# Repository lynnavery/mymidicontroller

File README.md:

# mymidicontroller
Simple 9 knob 10 key midi controller design using teensy and no mux/adc expanders

## Mockup

## BOM
| Qty | Part |
|---|---|
| 1 | Teensy 4.1 with headers |
| 2 | Custom PCB
| 1 | Jumper wires Female/Male 300mm pack of 40 |
| 1 | Strip of standard headers (2.54mm) for 22 total
| 1 | USB A to Micro-B cable |
| 9 | 10K linear pot PTV09A-4020U-B103 |
| 10 | Cherry MX/knockoff switch (any color) |
| 10 | Keycaps |
| 1 | 0.96in OLED I2C 4-pin white character display |
| 1 | Enclosure and front panel (3d printed) |

If I decide to do an expander for the extra teensy io
| Qty | Part |
|---|---|
| 1 | Panel-mount D-sub or aviation connector |
| 6 | Series resistors 220ohm-1k for expander lines |

## Circuit diagram

## References
- https://www.pjrc.com/teensy/td_midi.html
- Library for teensy midi controllers https://github.com/joshnishikawa/MIDIcontroller
- another midi library for teensy https://tomashg.com/?p=854
- another midi library https://tttapa.github.io/Control-Surface/Doxygen/index.html

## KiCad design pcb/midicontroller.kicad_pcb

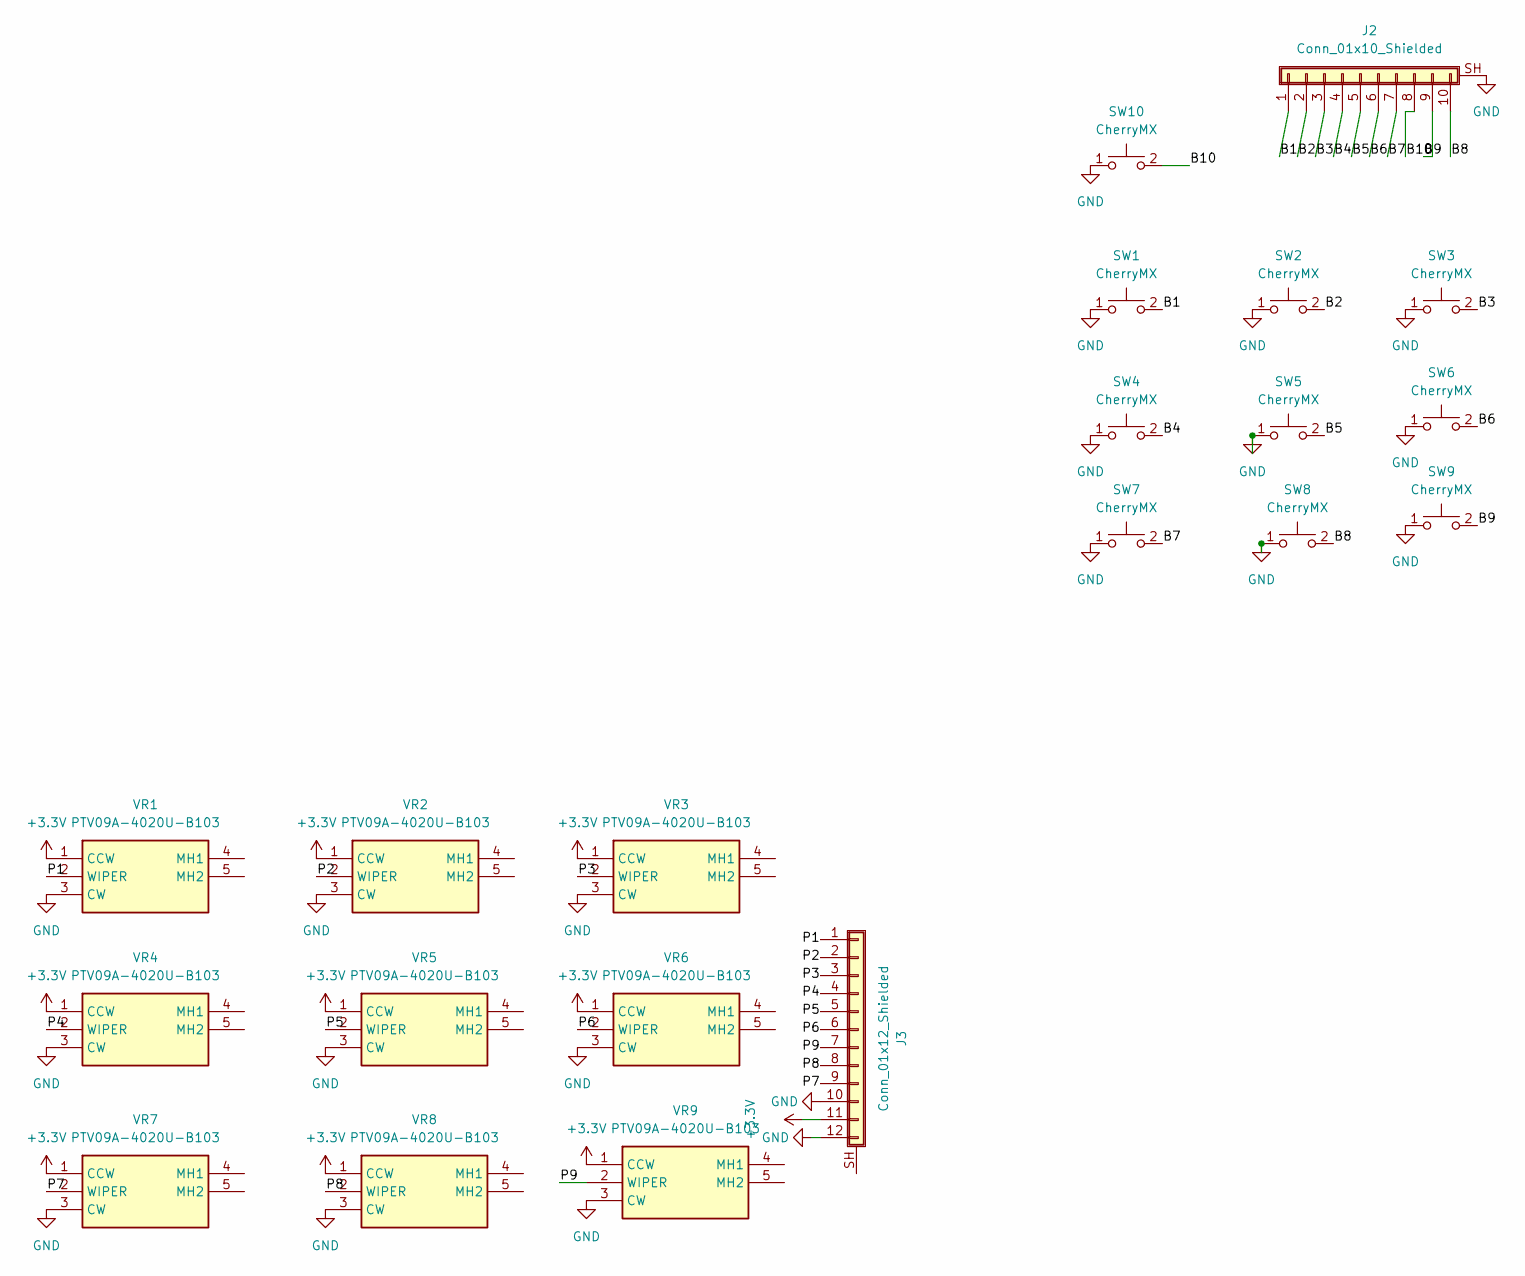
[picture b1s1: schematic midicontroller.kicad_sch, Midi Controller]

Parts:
J2: Conn_01x10_Shielded; PinHeader_1x11_P2.54mm_Vertical
J3: Conn_01x12_Shielded; PinHeader_1x12_P2.54mm_Vertical
SW1, SW2, SW3, SW4, SW5, SW6, SW7, SW8, SW9, SW10: CherryMX; SW_Cherry_MX_1.00u_PCB
VR1, VR2, VR3, VR4, VR5, VR6, VR7, VR8, VR9: PTV09A-4020U-B103; Manufacturer_Part_Number PTV09A-4020U-B103; Mouser Part Number 652-PTV09A-4020UB103

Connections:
+3.3V: J3.11, VR1.1 (CCW), VR2.1 (CCW), VR3.1 (CCW), VR4.1 (CCW), VR5.1 (CCW), VR6.1 (CCW), VR7.1 (CCW), VR8.1 (CCW), VR9.1 (CCW)
/B1: J2.1, SW1.2
/B2: J2.2, SW2.2
/B3: J2.3, SW3.2
/B4: J2.4, SW4.2
/B5: J2.5, SW5.2
/B6: J2.6, SW6.2
/B7: J2.7, SW7.2
/B8: J2.10, SW8.2
/B9: J2.9, SW9.2
/B10: J2.8, SW10.2
/P1: J3.1, VR1.2 (WIPER)
/P2: J3.2, VR2.2 (WIPER)
/P3: J3.3, VR3.2 (WIPER)
/P4: J3.4, VR4.2 (WIPER)
/P5: J3.5, VR5.2 (WIPER)
/P6: J3.6, VR6.2 (WIPER)
/P7: J3.9, VR7.2 (WIPER)
/P8: J3.8, VR8.2 (WIPER)
/P9: J3.7, VR9.2 (WIPER)
GND: J2.SH (Shield), J3.10, J3.12, SW1.1, SW2.1, SW3.1, SW4.1, SW5.1, SW6.1, SW7.1, SW8.1, SW9.1, SW10.1, VR1.3 (CW), VR2.3 (CW), VR3.3 (CW), VR4.3 (CW), VR5.3 (CW), VR6.3 (CW), VR7.3 (CW), VR8.3 (CW), VR9.3 (CW)

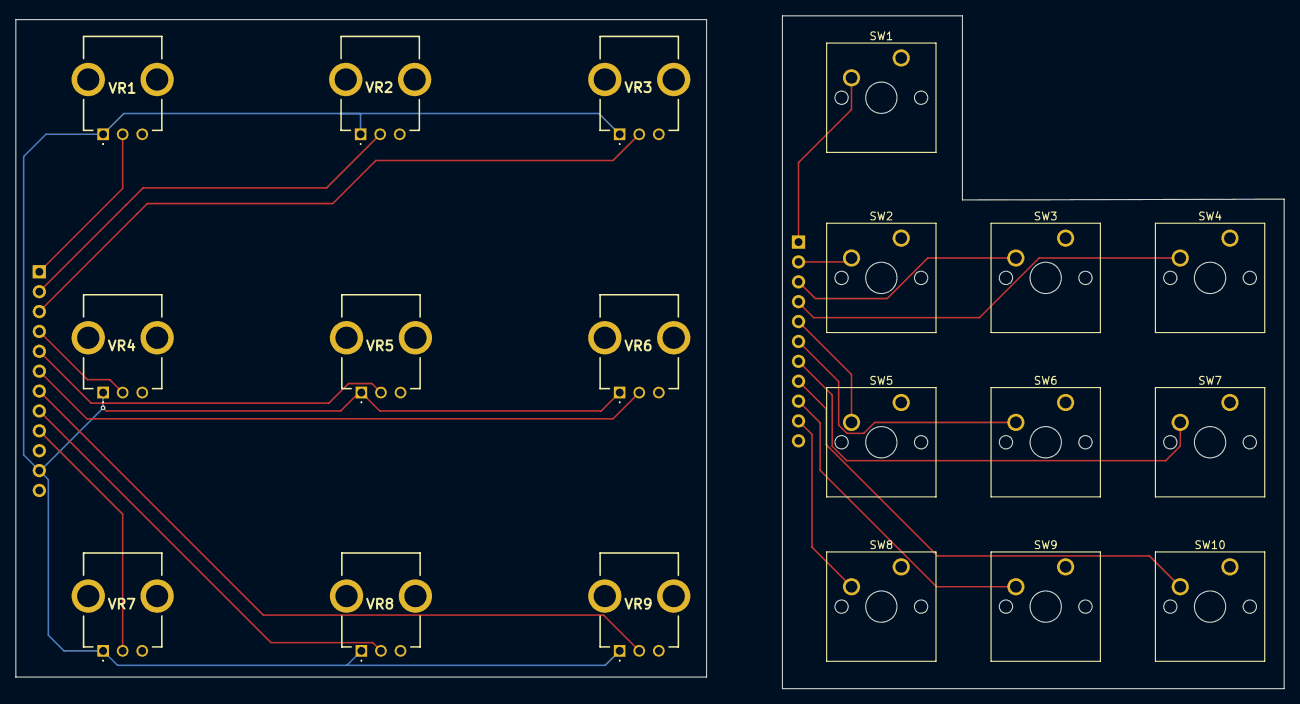
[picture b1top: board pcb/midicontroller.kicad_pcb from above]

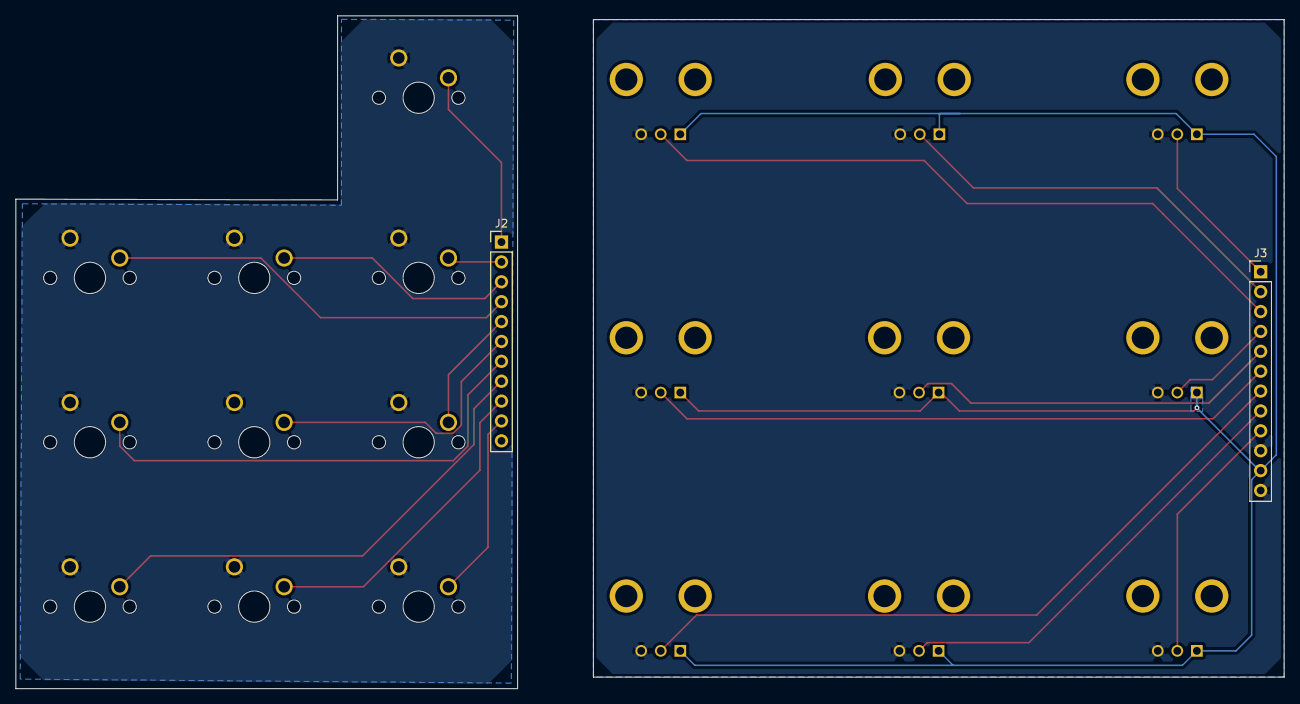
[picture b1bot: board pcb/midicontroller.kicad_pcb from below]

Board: 2 copper layers, 162.0 x 86.0 mm, 21 parts (2 on the bottom side), 21 nets.

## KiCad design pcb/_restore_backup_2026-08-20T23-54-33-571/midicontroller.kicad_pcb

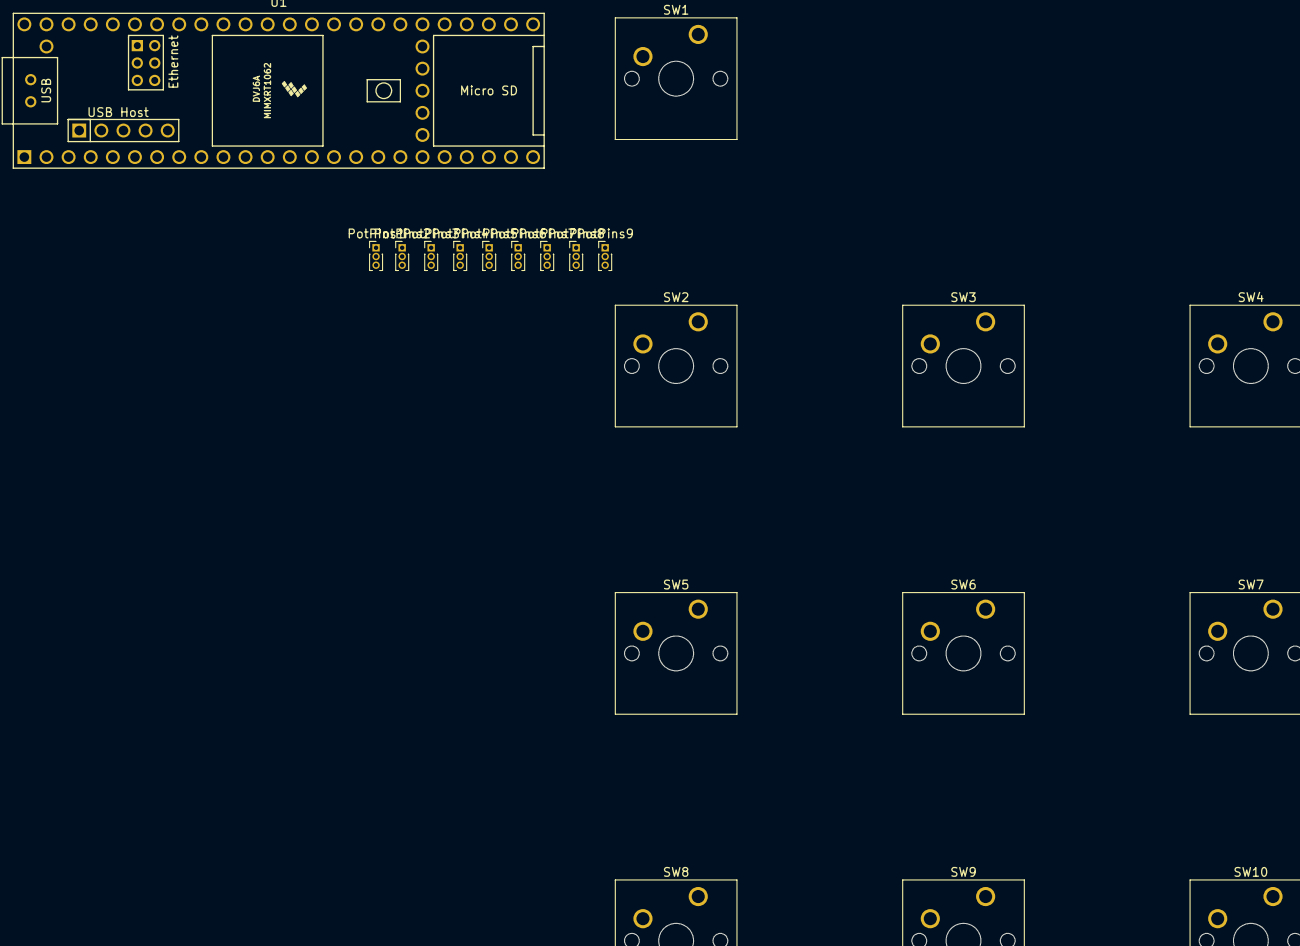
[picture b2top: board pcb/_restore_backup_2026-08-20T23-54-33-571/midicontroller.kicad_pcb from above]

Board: 2 copper layers, 20 parts (0 on the bottom side), 20 nets, no tracks yet.

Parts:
PotPins1, PotPins2, PotPins3, PotPins4, PotPins5, PotPins6, PotPins7, PotPins8, PotPins9: PinHeader_1x03_P1.00mm_Vertical
SW1, SW2, SW3, SW4, SW5, SW6, SW7, SW8, SW9, SW10: CherryMX; SW_Cherry_MX_1.00u_PCB
U1: Teensy4.1; Teensy41

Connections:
+3.3V: PotPins1.1 (Pot3v), PotPins2.1 (Pot3v), PotPins3.1 (Pot3v), PotPins4.1 (Pot3v), PotPins5.1 (Pot3v), PotPins6.1 (Pot3v), PotPins7.1 (Pot3v), PotPins8.1 (Pot3v), PotPins9.1 (Pot3v), U1.48 (VIN)
/B2: SW1.2, U1.3 (1_TX1_CTX2_MISO1)
/B3: SW2.2, U1.4 (2_OUT2)
/B4: SW3.2, U1.5 (3_LRCLK2)
/B5: SW4.2, U1.6 (4_BCLK2)
/B6: SW5.2, U1.7 (5_IN2)
/B7: SW6.2, U1.8 (6_OUT1D)
/B8: SW7.2, U1.9 (7_RX2_OUT1A)
/B9: SW8.2, U1.10 (8_TX2_IN1)
/B10: SW9.2, U1.11 (9_OUT1C)
/P1: PotPins1.2 (PotWiper), U1.30 (38_CS1_IN1)
/P2: PotPins3.2 (PotWiper), U1.31 (39_MISO1_OUT1A)
/P3: PotPins4.2 (PotWiper), U1.32 (40_A16)
/P5: PotPins5.2 (PotWiper), U1.36 (14_A0_TX3_SPDIF_OUT)
/P6: PotPins6.2 (PotWiper), U1.37 (15_A1_RX3_SPDIF_IN)
/P7: PotPins7.2 (PotWiper), U1.38 (16_A2_RX4_SCL1)
/P8: PotPins8.2 (PotWiper), U1.39 (17_A3_TX4_SDA1)
/P9: PotPins9.2 (PotWiper), U1.42 (20_A6_TX5_LRCLK1)
GND: PotPins1.3 (PotGND), PotPins2.3 (PotGND), PotPins3.3 (PotGND), PotPins4.3 (PotGND), PotPins5.3 (PotGND), PotPins6.3 (PotGND), PotPins7.3 (PotGND), PotPins8.3 (PotGND), PotPins9.3 (PotGND), SW1.1, SW2.1, SW3.1, SW4.1, SW5.1, SW6.1, SW7.1, SW8.1, SW9.1, SW10.1, U1.47 (GND)
P4: PotPins2.2 (PotWiper), U1.33 (41_A17)
